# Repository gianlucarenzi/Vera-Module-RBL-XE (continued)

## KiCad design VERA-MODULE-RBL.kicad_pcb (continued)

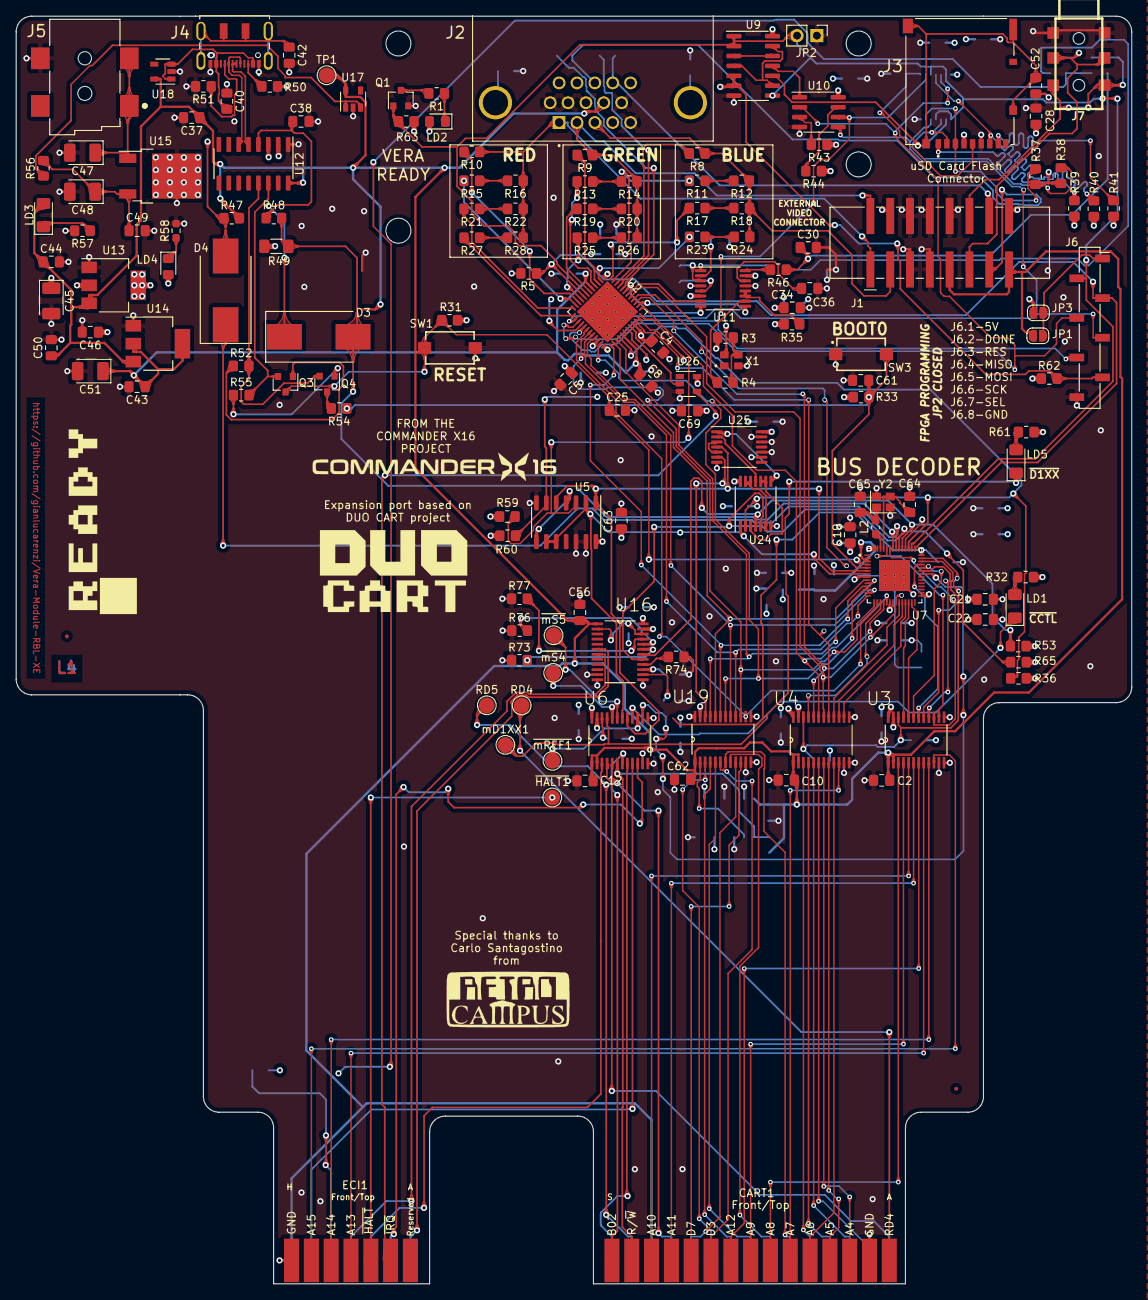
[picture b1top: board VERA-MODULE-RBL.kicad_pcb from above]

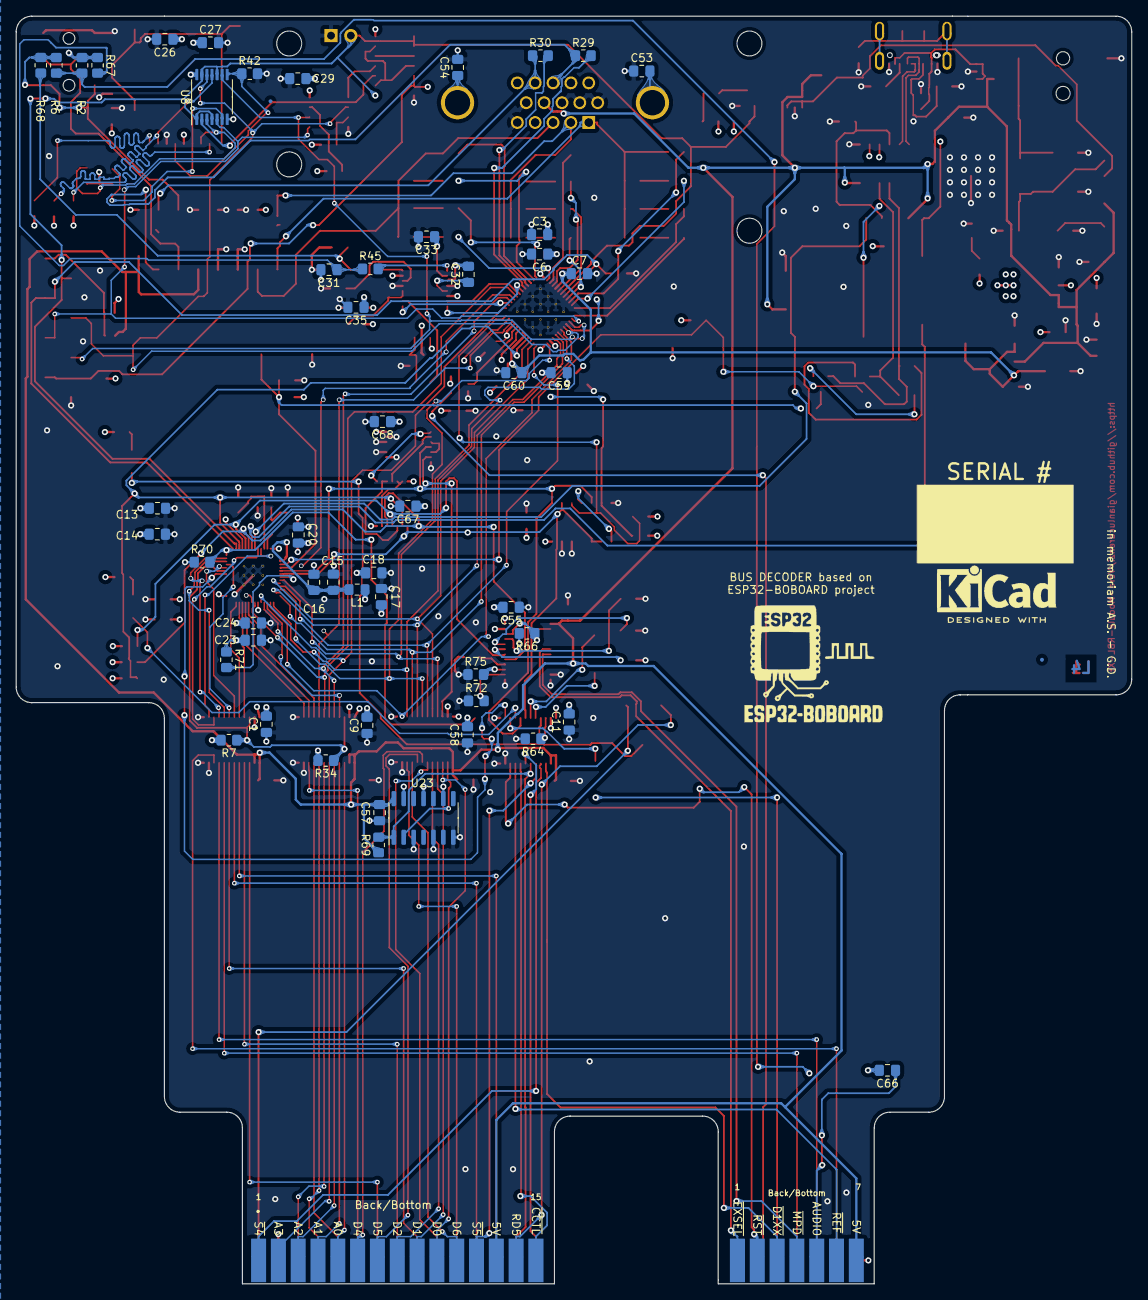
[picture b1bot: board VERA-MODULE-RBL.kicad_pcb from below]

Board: 4 copper layers, 143.0 x 162.5 mm, 213 parts (57 on the bottom side), 195 nets.

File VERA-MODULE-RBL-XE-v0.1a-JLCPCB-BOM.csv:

Comment,Designator,Footprint,LCSC
10uF,"C13,C15,C17,C19,C21,C24",Capacitor_SMD:C_1206_3216Metric_Pad1.33x1.80mm_HandSolder,C363964
100nF,"C14,C16,C18,C20,C22,C23,C25,C27,C28,C29,C38,C40,C42,C44,C46,C49,C50,C52,C53,C54",Capacitor_SMD:C_1206_3216Metric_Pad1.33x1.80mm_HandSolder,C2858001
4.7uF,"C26,C34,C35",Capacitor_SMD:C_1206_3216Metric_Pad1.33x1.80mm_HandSolder,C33546020
2.2uF,C36,Capacitor_SMD:C_1206_3216Metric_Pad1.33x1.80mm_HandSolder,C577211
22uF,C37,Capacitor_SMD:C_1206_3216Metric_Pad1.33x1.80mm_HandSolder,C6119967
20pF,"C39,C41",Capacitor_SMD:C_1206_3216Metric_Pad1.33x1.80mm_HandSolder,C5137576
1uF,"C1,C2,C3,C4,C5,C6,C7,C8,C9,C10,C11,C12,C30,C31,C32,C33,C43,C55,C56,C57,C58,C59,C60",Capacitor_SMD:C_1206_3216Metric_Pad1.33x1.80mm_HandSolder,C377070
10uF-35V,C47,Capacitor_Tantalum_SMD:CP_EIA-3528-12_Kemet-T_Pad1.50x2.35mm_HandSolder,C8017
10uF-20V,"C45,C48,C51",Capacitor_Tantalum_SMD:CP_EIA-3528-12_Kemet-T_Pad1.50x2.35mm_HandSolder,C8017
DIOSCH20V,"D3,D4",Diode_SMD:D_SMC_Handsoldering,C236151
CONN_SMD_02x08_Odd_Even_2.54mm,J1,RetroBitLab:PinSocket_2x08_P2.54mm_Vertical_SMD,C3975153
DS1038-15FBNSiA74-0CC,J2,RetroBitLab:CONNFLY_DS1038-15FBNSIA74-0CC,C75754
CONN_DM3AT-SF-PEJM5,J3,RetroBitLab:HRS_DM3AT-SF-PEJM5,C114218
DX07S016JA1R1500,J4,RetroBitLab:JAE_DX07S016JA1R1500,C3197885
PJ-002AH-SMT-TR,J5,RetroBitLab:CUI_PJ-002AH-SMT-TR,C22434687
CONN_SMD_01x08_Staggered_2.54mm,J6,Connector_PinSocket_2.54mm:PinSocket_1x08_P2.54mm_Vertical_SMD_Pin1Right,C42380985
SJ-3523-SMT-TR,J7,RetroBitLab:CONN_AUDIO_CUI_SJ-3523-SMT-TR,C4991872
FB0805100R100MHZ4A,L1,Inductor_SMD:L_0805_2012Metric_Pad1.15x1.40mm_HandSolder,C15957
RED,"LD1,LD3,LD5",LED_SMD:LED_1206_3216Metric_Pad1.42x1.75mm_HandSolder,C965822
GREEN,"LD2,LD4",LED_SMD:LED_0805_2012Metric_Pad1.15x1.40mm_HandSolder,C84260
MOSFET-BSS138-SOT-23,Q1,Package_TO_SOT_SMD:SOT-23,C82045
"BC817,SOT-23","Q3,Q4",Package_TO_SOT_SMD:SOT-23,C20069154
2K7,R1,Resistor_SMD:R_1206_3216Metric_Pad1.30x1.75mm_HandSolder,C6757641
2K,"R11,R13,R15",Resistor_SMD:R_1206_3216Metric_Pad1.30x1.75mm_HandSolder,C133543
150R,"R12,R14,R16",Resistor_SMD:R_1206_3216Metric_Pad1.30x1.75mm_HandSolder,C137387
160R,"R18,R20,R22",Resistor_SMD:R_1206_3216Metric_Pad1.30x1.75mm_HandSolder,C2933602
910R,"R17,R19,R21",Resistor_SMD:R_1206_3216Metric_Pad1.30x1.75mm_HandSolder,C5713461
27R,"R24,R26,R28",Resistor_SMD:R_1206_3216Metric_Pad1.30x1.75mm_HandSolder,C17946
820R,"R29,R30",Resistor_SMD:R_1206_3216Metric_Pad1.30x1.75mm_HandSolder,C2933759
50R,"R3,R4",Resistor_SMD:R_1206_3216Metric_Pad1.30x1.75mm_HandSolder,C2984401
330R,"R32,R61",Resistor_SMD:R_1206_3216Metric_Pad1.30x1.75mm_HandSolder,C114944
10K,"R33,R34,R62",Resistor_SMD:R_0805_2012Metric_Pad1.20x1.40mm_HandSolder,C84376
47K,"R37,R38,R39,R40,R41,R42,R43,R44",Resistor_SMD:R_1206_3216Metric_Pad1.30x1.75mm_HandSolder,C25833
560R,"R45,R46,R67,R68",Resistor_SMD:R_1206_3216Metric_Pad1.30x1.75mm_HandSolder,C2759125
10K,"R2,R5,R6,R7,R35,R36,R47,R48,R53,R63,R64,R65,R66",Resistor_SMD:R_1206_3216Metric_Pad1.30x1.75mm_HandSolder,C17902
5K1,"R50,R51",Resistor_SMD:R_1206_3216Metric_Pad1.30x1.75mm_HandSolder,C163372
220R,R54,Resistor_SMD:R_1206_3216Metric_Pad1.30x1.75mm_HandSolder,C137353
2K2,"R52,R55",Resistor_SMD:R_1206_3216Metric_Pad1.30x1.75mm_HandSolder,C114933
0R,R56,Resistor_SMD:R_1206_3216Metric_Pad1.30x1.75mm_HandSolder,C17888
510R,"R23,R25,R27,R57",Resistor_SMD:R_1206_3216Metric_Pad1.30x1.75mm_HandSolder,C2933720
330R,R58,Resistor_SMD:R_0603_1608Metric_Pad0.98x0.95mm_HandSolder,C105881
4K7,"R31,R59,R60",Resistor_SMD:R_1206_3216Metric_Pad1.30x1.75mm_HandSolder,C17936
4K3,"R8,R9,R10",Resistor_SMD:R_1206_3216Metric_Pad1.30x1.75mm_HandSolder,C2933704
SPST2P,SW1,RetroBitLab:SPST-7.3x3.9x2.5-WUERTH-434121025816,C318911
"SPST_SWITCH_SMD_4P,4.1x5.4mm",SW2,RetroBitLab:SW_DIP_SPSTx02_DSHP02TS-S,C319052
W25Q16JVSNIQ,U10,Package_SO:SOIC-8_3.9x4.9mm_P1.27mm,C2456211
WM8524CGEDT,U11,Package_SO:TSSOP-16_4.4x5mm_P0.65mm,C146242
USBCH340T,U12,Package_SO:SSOP-20_5.3x7.2mm_P0.65mm,C8689
AMS1117-3.3,U13,Package_TO_SOT_SMD:SOT-223-3_TabPin2,C6186
AMS1117-1.2,U14,Package_TO_SOT_SMD:SOT-223-3_TabPin2,C347218
L7805,U15,Package_TO_SOT_SMD:TO-252-2,C110908
MAX40200AUK,"U17,U18",Package_TO_SOT_SMD:SOT-23-5,C47118006
ICE40UP5K-SG48ITR,U2,RetroBitLab:QFN-48-1EP_7x7mm_P0.5mm_EP5.6x5.6mm,C2678152
TXS0108EPW,"U1,U3,U4,U6,U16",Package_SO:TSSOP-20_4.4x6.5mm_P0.65mm,C17206
CD4011B,"U5,U9",Package_SO:SOIC-14_3.9x8.7mm_P1.27mm,C194334
ESP32-PICO-D4,U7,RetroBitLab:ESP32-PICO-D4,C193707
"74CBTLV3126PW,118",U8,Package_SO:TSSOP-14_4.4x5mm_P0.65mm,C543078
ECS-2033-250-BN,X1,RetroBitLab:OSC_ECS-2033-250-BN,C2441279
12MHzC,Y1,Crystal:Crystal_SMD_EuroQuartz_MT-4Pin_3.2x2.5mm,C9002

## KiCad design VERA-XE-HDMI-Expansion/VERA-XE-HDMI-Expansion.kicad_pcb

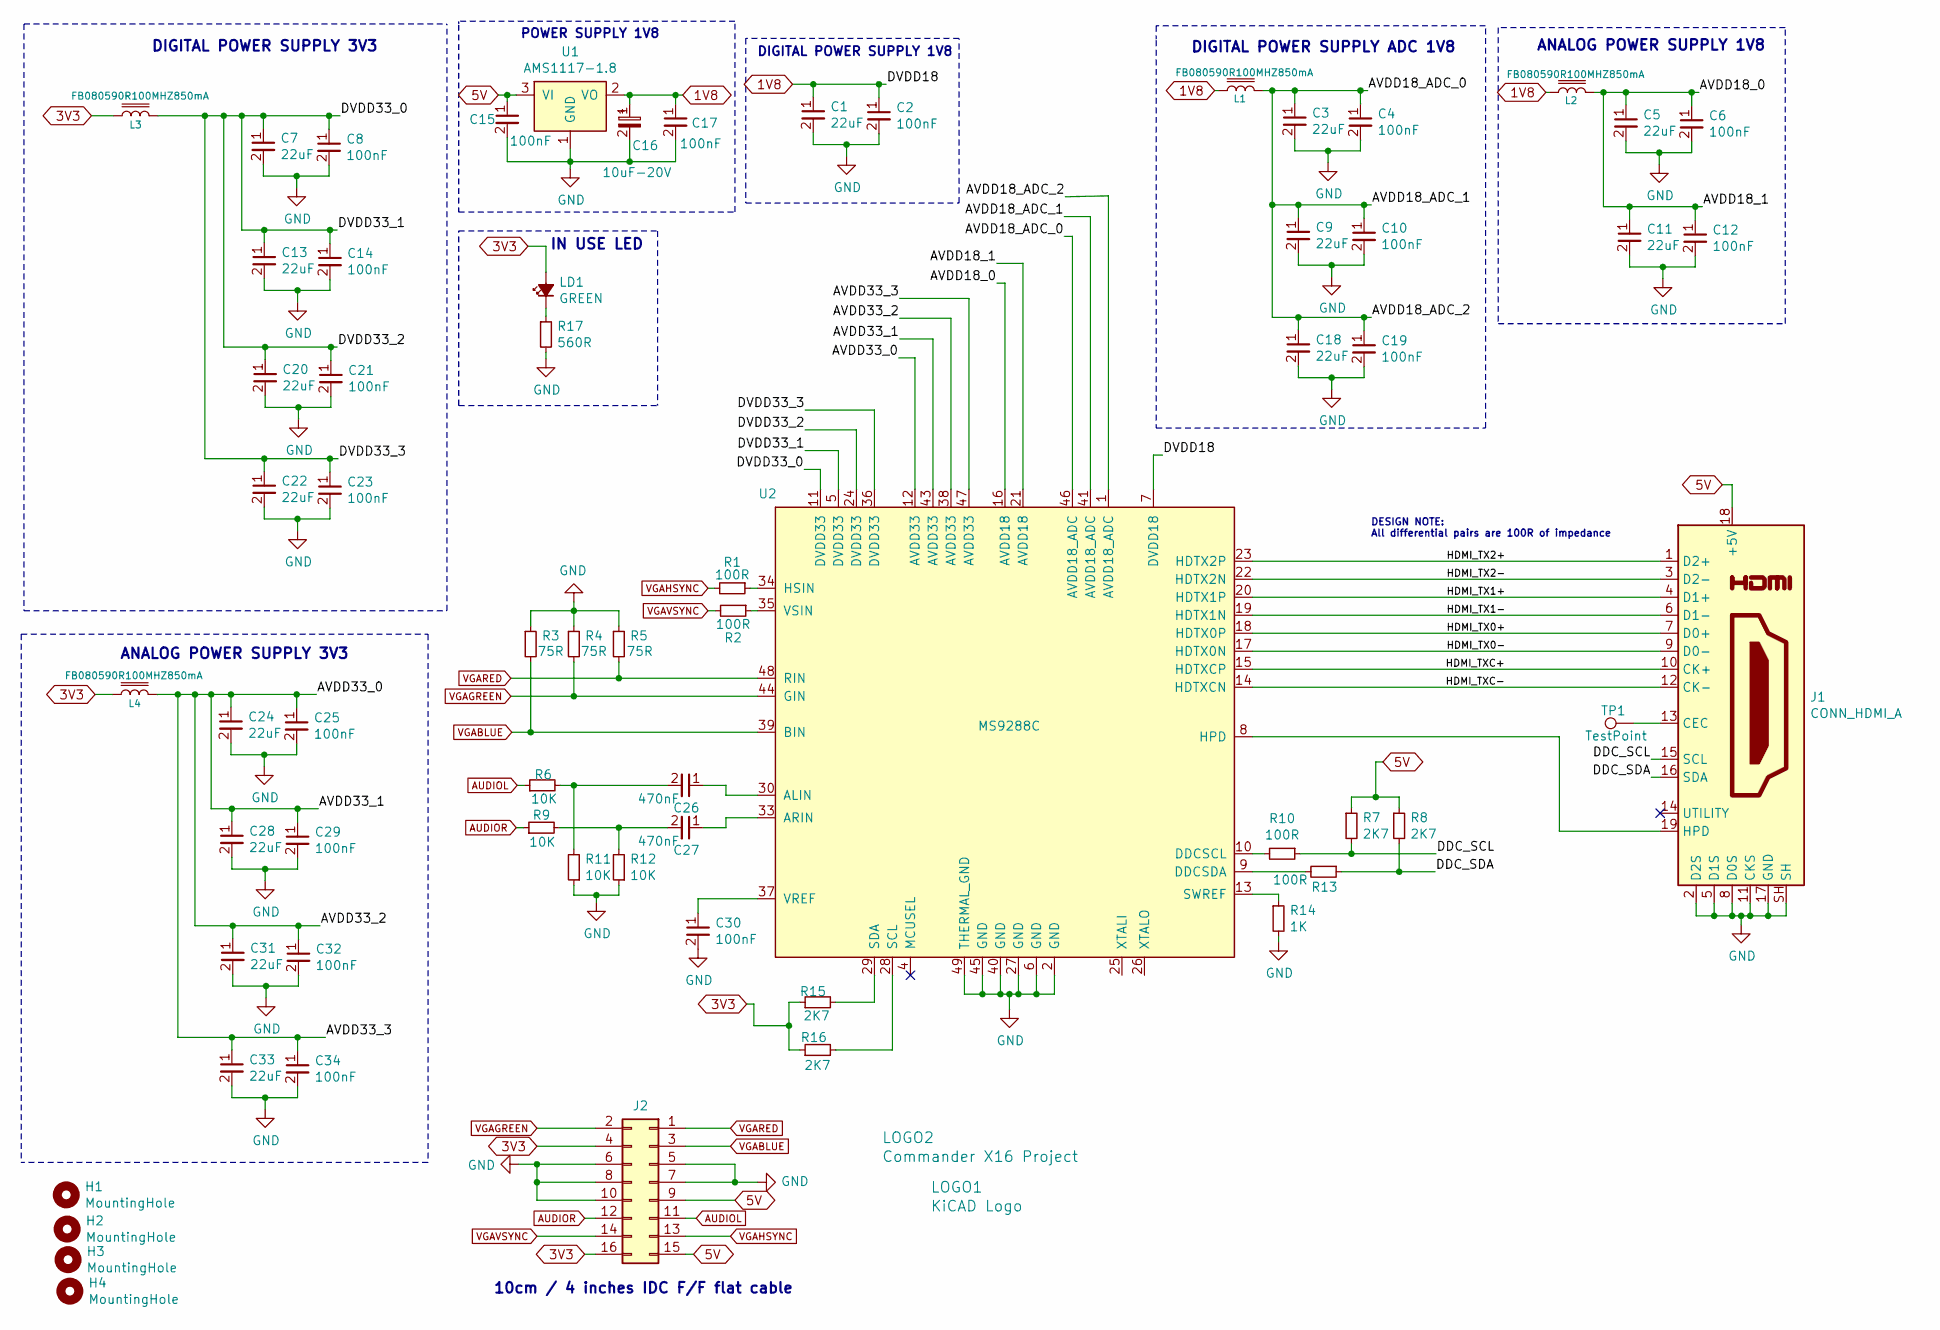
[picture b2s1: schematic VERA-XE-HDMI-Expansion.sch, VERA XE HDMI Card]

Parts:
C1, C3, C5, C7, C9, C11, C13, C18, C20, C22, C24, C28, C31, C33: 22uF; C_0805_2012Metric_Pad1.18x1.45mm_HandSolder; LCSC C86817
C2, C4, C6, C8, C10, C12, C14, C15, C17, C19, C21, C23, C25, C29, C30, C32, C34: 100nF; C_0805_2012Metric_Pad1.18x1.45mm_HandSolder; LCSC C840116
C16: 10uF-20V; CP_EIA-3528-12_Kemet-T_Pad1.50x2.35mm_HandSolder; LCSC C8017
C26, C27: 470nF; C_0805_2012Metric_Pad1.18x1.45mm_HandSolder; LCSC C106843
H1, H2, H3, H4: MountingHole; MountingHole_3.2mm_M3
J1: CONN_HDMI_A; CONN_HDMI-A; LCSC C720616
J2: CONN_SMD_HEADER_BOX_02x08_Odd_Even_2.54mm; PinHeader_BOX_2x08_P2.54mm_Vertical_SMD; LCSC C2685064
L1, L2, L3, L4: FB080590R100MHZ850mA; L_0805_2012Metric_Pad1.15x1.40mm_HandSolder; LCSC C50325938
LD1: GREEN; LED_0805_2012Metric_Pad1.15x1.40mm_HandSolder; LCSC C84260
LOGO1: KiCAD Logo; KiCad-Logo2_6mm_SilkScreen
LOGO2: Commander X16 Project; x16logo
R1, R2, R10, R13: 100R; R_0805_2012Metric_Pad1.20x1.40mm_HandSolder; LCSC C17408
R3, R4, R5: 75R; R_0805_2012Metric_Pad1.20x1.40mm_HandSolder; LCSC C20142801
R6, R9, R11, R12: 10K; R_0805_2012Metric_Pad1.20x1.40mm_HandSolder; LCSC C84376
R7, R8, R15, R16: 2K7; R_0603_1608Metric_Pad0.98x0.95mm_HandSolder; LCSC C491210
R14: 1K; R_0805_2012Metric_Pad1.20x1.40mm_HandSolder; LCSC C17513
R17: 560R; R_0603_1608Metric_Pad0.98x0.95mm_HandSolder; LCSC C114629
TP1: TestPoint; TestPoint_Pad_1.0x1.0mm
U1: AMS1117-1.8; SOT-223-3_TabPin2; LCSC C6185
U2: MS9288C; LCSC C2914316

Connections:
1V8: C1.1, C2.1, C16.1, C17.1, L1.1, L2.1, U1.2 (VO), U2.7 (DVDD18)
3V3: J2.4, J2.16, L3.1, L4.1, LD1.2 (A), R15.1, R16.1
5V: C15.1, J1.18 (+5V), J2.9, J2.15, R7.1, R8.1, U1.3 (VI)
/AVDD18_0: C5.1, C6.1, C11.1, C12.1, L2.2, U2.16 (AVDD18), U2.21 (AVDD18)
/AVDD18_ADC_0: C3.1, C4.1, C9.1, C10.1, C18.1, C19.1, L1.2, U2.1 (AVDD18_ADC), U2.41 (AVDD18_ADC), U2.46 (AVDD18_ADC)
/AVDD33_0: C24.1, C25.1, C28.1, C29.1, C31.1, C32.1, C33.1, C34.1, L4.2, U2.12 (AVDD33), U2.38 (AVDD33), U2.43 (AVDD33), U2.47 (AVDD33)
/DDC_SCL: J1.15 (SCL), R7.2, R10.1
/DDC_SDA: J1.16 (SDA), R8.2, R13.1
/DVDD33_0: C7.1, C8.1, C13.1, C14.1, C20.1, C21.1, C22.1, C23.1, L3.2, U2.5 (DVDD33), U2.11 (DVDD33), U2.24 (DVDD33), U2.36 (DVDD33)
/HDMI_TX0+: J1.7 (D0+), U2.18 (HDTX0P)
/HDMI_TX0-: J1.9 (D0-), U2.17 (HDTX0N)
/HDMI_TX1+: J1.4 (D1+), U2.20 (HDTX1P)
/HDMI_TX1-: J1.6 (D1-), U2.19 (HDTX1N)
/HDMI_TX2+: J1.1 (D2+), U2.23 (HDTX2P)
/HDMI_TX2-: J1.3 (D2-), U2.22 (HDTX2N)
/HDMI_TXC+: J1.10 (CK+), U2.15 (HDTXCP)
/HDMI_TXC-: J1.12 (CK-), U2.14 (HDTXCN)
AUDIOL: J2.11, R6.1
AUDIOR: J2.12, R9.1
GND: C1.2, C2.2, C3.2, C4.2, C5.2, C6.2, C7.2, C8.2, C9.2, C10.2, C11.2, C12.2, C13.2, C14.2, C15.2, C16.2, C17.2, C18.2, C19.2, C20.2, C21.2, C22.2, C23.2, C24.2, C25.2, C28.2, C29.2, C30.2, C31.2, C32.2, C33.2, C34.2, J1.2 (D2S), J1.5 (D1S), J1.8 (D0S), J1.11 (CKS), J1.17 (GND), J1.SH, J2.5, J2.6, J2.7, J2.8, J2.10, R3.1, R4.1, R5.1, R11.1, R12.1, R14.2, R17.2, U1.1 (GND), U2.2 (GND), U2.6 (GND), U2.27 (GND), U2.40 (GND), U2.45 (GND), U2.49 (THERMAL_GND)
unnamed: C26.1, U2.30 (ALIN)
unnamed: C26.2, R6.2, R11.2
unnamed: C27.1, U2.33 (ARIN)
unnamed: C27.2, R9.2, R12.2
unnamed: C30.1, U2.37 (VREF)
unnamed: J1.13 (CEC), TP1.1
unnamed: J1.19 (HPD), U2.8 (HPD)
unnamed: LD1.1 (K), R17.1
unnamed: R1.1, U2.34 (HSIN)
unnamed: R2.1, U2.35 (VSIN)
unnamed: R10.2, U2.10 (DDCSCL)
unnamed: R13.2, U2.9 (DDCSDA)
unnamed: R14.1, U2.13 (SWREF)
unnamed: R15.2, U2.29 (SDA)
unnamed: R16.2, U2.28 (SCL)
VGABLUE: J2.3, R3.2, U2.39 (BIN)
VGAGREEN: J2.2, R4.2, U2.44 (GIN)
VGAHSYNC: J2.13, R1.2
VGARED: J2.1, R5.2, U2.48 (RIN)
VGAVSYNC: J2.14, R2.2

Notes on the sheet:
DIGITAL POWER SUPPLY 3V3
ANALOG POWER SUPPLY 3V3
DIGITAL POWER SUPPLY 1V8
DIGITAL POWER SUPPLY ADC 1V8
ANALOG POWER SUPPLY 1V8
DESIGN NOTE: All differential pairs are 100R of impedance
POWER SUPPLY 1V8
10cm / 4 inches IDC F/F flat cable
IN USE LED

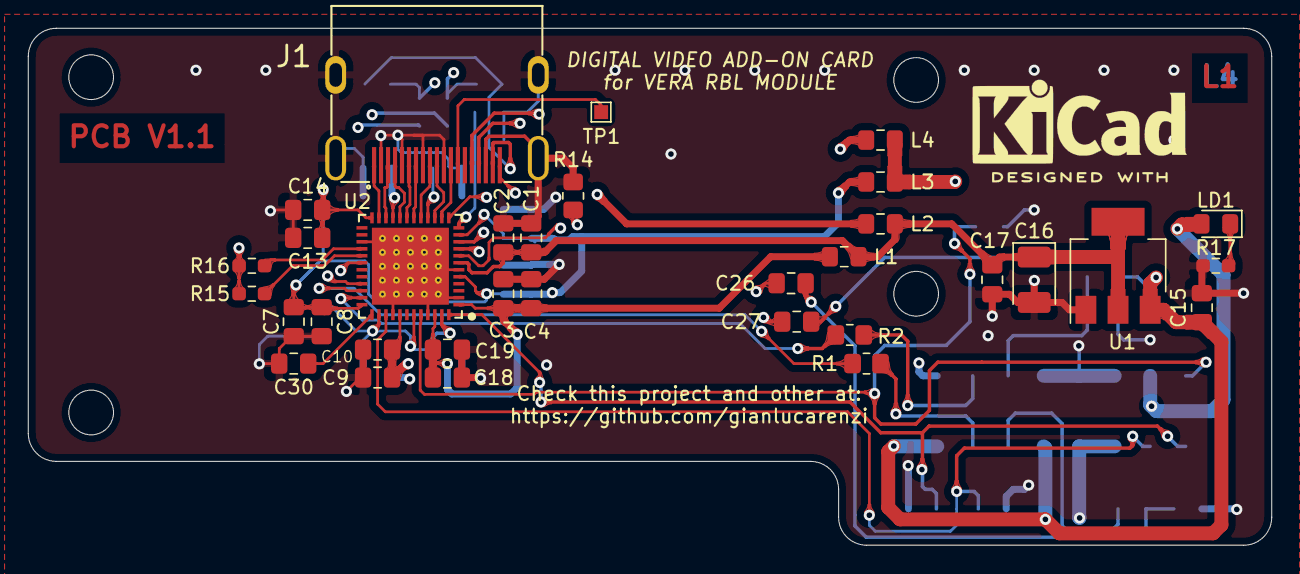
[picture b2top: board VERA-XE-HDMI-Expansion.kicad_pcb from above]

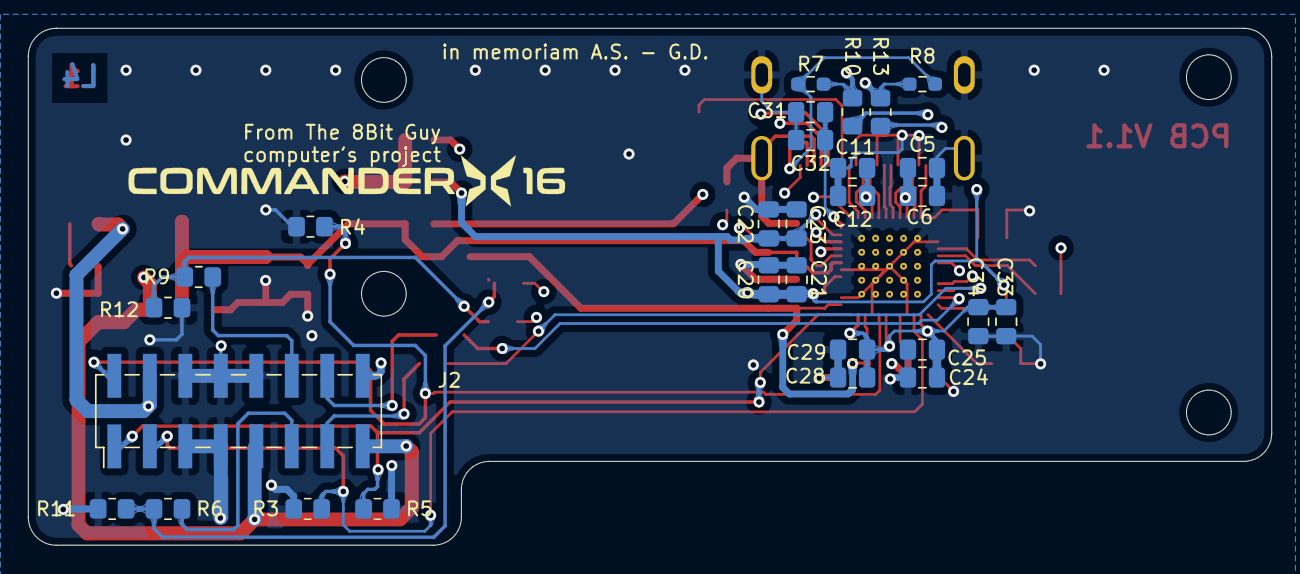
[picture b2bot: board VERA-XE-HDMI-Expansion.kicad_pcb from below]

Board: 4 copper layers, 89.0 x 37.0 mm, 67 parts (29 on the bottom side), 40 nets.

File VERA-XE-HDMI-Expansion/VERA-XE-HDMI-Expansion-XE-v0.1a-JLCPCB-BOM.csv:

Comment,Designator,Footprint,LCSC
10uF-20V,C16,Capacitor_Tantalum_SMD:CP_EIA-3528-12_Kemet-T_Pad1.50x2.35mm_HandSolder,C8017
470nF,"C26,C27",Capacitor_SMD:C_0805_2012Metric_Pad1.18x1.45mm_HandSolder,C106843
22uF,"C1,C3,C5,C7,C9,C11,C13,C18,C20,C22,C24,C28,C31,C33",Capacitor_SMD:C_0805_2012Metric_Pad1.18x1.45mm_HandSolder,C86817
100nF,"C2,C4,C6,C8,C10,C12,C14,C15,C17,C19,C21,C23,C25,C29,C30,C32,C34",Capacitor_SMD:C_0805_2012Metric_Pad1.18x1.45mm_HandSolder,C840116
CONN_HDMI_A,J1,RetroBitLab:CONN_HDMI-A,C720616
CONN_SMD_HEADER_02x08_Odd_Even_2.54mm,J2,Connector_PinHeader_2.54mm:PinHeader_2x08_P2.54mm_Vertical_SMD,C32713288
FB080590R100MHZ850mA,"L1,L2,L3,L4",Inductor_SMD:L_0805_2012Metric_Pad1.15x1.40mm_HandSolder,C50325938
GREEN,LD1,LED_SMD:LED_0805_2012Metric_Pad1.15x1.40mm_HandSolder,C84260
1K,R14,Resistor_SMD:R_0805_2012Metric_Pad1.20x1.40mm_HandSolder,C17513
2K7,"R7,R8,R15,R16",Resistor_SMD:R_0603_1608Metric_Pad0.98x0.95mm_HandSolder,C491210
560R,R17,Resistor_SMD:R_0603_1608Metric_Pad0.98x0.95mm_HandSolder,C114629
100R,"R1,R2,R10,R13",Resistor_SMD:R_0805_2012Metric_Pad1.20x1.40mm_HandSolder,C17408
75R,"R3,R4,R5",Resistor_SMD:R_0805_2012Metric_Pad1.20x1.40mm_HandSolder,C20142801
10K,"R6,R9,R11,R12",Resistor_SMD:R_0805_2012Metric_Pad1.20x1.40mm_HandSolder,C84376
AMS1117-1.8,U1,Package_TO_SOT_SMD:SOT-223-3_TabPin2,C6185
MS9288C,U2,RetroBitLab:MS9288C,C2914316

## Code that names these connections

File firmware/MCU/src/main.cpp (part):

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 * =========================================================================== */

/* --- Bank 0 Signals (GPIO 0-31) --- */
#define PIN_PHI2        1    /* CPU Clock Phase 2 (Pin 6) */
#define PIN_RW          2    /* Read/Write, High = Read (Pin 7) */

/* D0-D7: GPIO 4 to 11 (Pins 9-16, contiguous in Bank 0): D0 = GPIO 4 */
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#define PIN_CDONE       39   /* Vera Programmed Status Input (Pin 44) */
#define PIN_DEV_SEL_N   40   /* Vera Chip Select Output (Pin 45, active LOW) */
#define PIN_EXTSEL_N    41   /* Atari MMU Disable Output (Pin 47, active LOW) */
#define PIN_MPD         42   /* Math Pack Disable — disables internal Atari Math Pack ROM $D800-$DFFF (Pin 48, active LOW) */
#define PIN_A14         45   /* Address Bit 14 (Pin 51) */
#define PIN_A15         46   /* Address Bit 15 (Pin 52) */
#define PIN_ABUS_OE_N   47   /* ~OE of U3 (A8-A15) and U4 (A0-A7), 10 kΩ pull-ups R7/R34 (Pin 37, active LOW) */
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 * (ee.get_gpio_in / ee.wr_mask_gpio_out bypass the APB bus: ~1 cycle).
 *
 * Input channels  (bit index in cpu_ll_read_dedic_gpio_in() result):
 *   Ch 0 = PHI2 (GPIO 1), Ch 1 = R/W (GPIO 2), Ch 2-7 = A10-A15
 *   The GPIO matrix feeds the dedicated inputs without taking the pins away:
 *   the same signals stay visible in GPIO.in / GPIO.in1.
 *
 * Output channels (bit index in cpu_ll_write_dedic_gpio_mask() mask/val):
 *   Ch 0 = DEV_SEL_N  (GPIO 40)  active LOW
 *   Ch 1 = EXTSEL_N   (GPIO 41)  active LOW
 *   Ch 2 = MPD        (GPIO 42)  active LOW
 *
 * Input and output channel spaces are independent on ESP32-S3.
 * Channel bits (DEDIC_IN_* / DEDIC_OUT_*) are defined in bus_decode.h.
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 * =========================================================================== */
#define LOG_RING_SIZE 64u   /* power of two */

#define EVT_LATCH 0   /* VCS/CCTL latch state change */
#define EVT_REG   1   /* VERA register ($D1xx) access */

/* flags: bit0=write(1)/read(0)  bit1=latch state (EVT_LATCH)  bit2=MPD asserted  bit3=EXTSEL asserted */
typedef struct
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}

/*
 * PHI2 edge waits: one ee.get_gpio_in and one bit branch per sample
 * (3 cycles), the shortest polling loop.  They return the last sample.
 */
static inline __attribute__((always_inline)) void wait_phi2_high(void)
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     * Input  bundle: [PHI2, R/W, A10..A15]       → input  ch 0-7
     * Output bundle: [DEV_SEL_N, EXTSEL_N, MPD]  → output ch 0-2
     */
    static const int dedic_in_pins[]  = { PIN_PHI2, PIN_RW, PIN_A10, PIN_A11,
                                          PIN_A12, PIN_A13, PIN_A14, PIN_A15 };
    static const int dedic_out_pins[] = { PIN_DEV_SEL_N, PIN_EXTSEL_N, PIN_MPD };
    dedic_gpio_bundle_handle_t dedic_in_bundle, dedic_out_bundle;
    const dedic_gpio_bundle_config_t in_cfg =
    {
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            {
                /* VERA drives the bus: sample it just before PHI2 falls. */
                uint32_t last = lo, now;
                while ((now = GPIO.in) & (1UL << PIN_PHI2))
                    last = now;
                uint8_t fl = 0x00;  /* read */
                if (!(c & DEDIC_OUT_MPD))    fl |= 0x04;
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    gpio_reset_pin((gpio_num_t)PIN_CDONE);     /* GPIO 39 */
    gpio_reset_pin((gpio_num_t)PIN_DEV_SEL_N); /* GPIO 40 */
    gpio_reset_pin((gpio_num_t)PIN_EXTSEL_N);  /* GPIO 41 */
    gpio_reset_pin((gpio_num_t)PIN_MPD);       /* GPIO 42 */

    /* Hold the VERA in reset immediately; it is released below.  The Atari
     * cannot be held (RST is the 130XE NE555 output, see PIN_ARST_IN). */
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    cfg.mode         = GPIO_MODE_INPUT;

    /* Bank 0 inputs: PHI2, RW, D0-D7, A0-A9 */
    cfg.pin_bit_mask = (1ULL << PIN_PHI2) | (1ULL << PIN_RW) | DBUS_MASK | ABUS_LO_MASK;
    gpio_config(&cfg);

    /* Bank 1 inputs: A10-A15, CDONE, Atari RST */
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    pinMode(PIN_DEV_SEL_N, OUTPUT);
    digitalWrite(PIN_DEV_SEL_N, HIGH);

    pinMode(PIN_MPD, OUTPUT);
    digitalWrite(PIN_MPD, HIGH);

    /*
     * VERA bring-up:
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
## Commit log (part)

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2025-09-10 Update to more available components by LCSC
2025-09-12 Removed level shifters by MOSFET
2025-09-17 Modified the 1.5V LDO to 1.2V LDO as in X65 and Vera Module projects. Added a 3.5mm audio jack stereo. To check if there are issues with the ATARI connected AUDIO Mixer
2025-09-17 Moved the FPGA programming box from vera-fpga-flash.sch
2025-09-18 First commit from RetroBit Lab Computer. This file will be ignored by Git, as it has hardcoded the path to the project.
2025-09-19 Update date on schematics
2025-09-19 Added two 560R resistors on the AUDIO_[L/R] lines as in X65 schematics Audio Resistor in line changed from 2K7 to 10K
2025-09-23 Update date on schematics Added a label for Serial Number (by hand)
2025-09-23 CD4011B instead of IC74HC00 NAND Gate (LCSC availability) The pinout is different! Added Label 2mmx1mm LBL1
2025-09-24 Frames added
2025-09-24 Update the programming section
2025-09-29 Changed the code for 330R 1206 from LCSC
2025-09-30 Fit all project schematics in an A4 size sheet
2025-09-30 Changed LCSC code for 27R
2025-10-02 Error
2025-10-06 optimized for execution time
2025-10-08 More code optimizations
2025-10-08 ANSI Color update
2025-10-17 Ignored fp-info-cache
2025-10-17 Needed for holes for spacers
2025-10-17 Updated messages
2025-10-17 Some capacitors changed from 1206 to 0805 due to shortage of the bigger ones
2025-10-20 Size changes. WIP
2025-10-23 Capacitor 10uF 0805 change LCSC code. These are more common
2025-10-23 Corrected a TearDrop manually
2025-10-27 Removed. Those should not be needed
2025-10-28 Added cleanup report
2025-10-28 Auto-generated
2025-10-29 Generated when exporting BOM from Schematics. This should be generated by a CLI
2025-10-29 Removed. Not needed now
2025-10-29 Ignore the cache.lib file
2025-10-29 Autogenerated v1.1
2025-10-29 Updated to new holes for the Digital Video Interface (HDMI?) and with rounded corners
2025-10-29 Python3 path for system
2025-10-29 Added more artifact to be ignored
2025-10-29 Ignored built executables (eeplot and eeshow)
2026-05-05 Updated for Datasheet
2026-05-08 Updated DEVID MASK to 0x80 (bit 7)
2026-05-08 Ignore intermediate artifact from build
2026-05-08 Maximum ROM Size is 2K ($0800)
2026-05-08 Typo and missing includes
2026-05-28 Date updated
2026-05-28 FPGA always deactive. It will be relased to run by MCU ESP32 when ready
2026-05-28 Need 9 bytes of address space to have more than 256 bytes of addressing (needed for External Device RAM Space)
2026-06-08 All Power Voltage references are by Global Label (5V and 3V3)
2026-06-08 after saving
2026-06-09 Add dual-MCU support (ESP32-S3FN8 + ESP32-classic) with QFN56 pin mapping
    - Rewrite main.cpp with #if MCU_ESP32_S3 / MCU_ESP32_CLASSIC blocks: separate
    pin defines, DBUS_MASK, DBUS_PINS[], decode_addr/data/offset_cctl, and
    gpio_config bitmasks for each target; build_drive_lut and Serial.begin use
    the MCU-specific constants at compile time
    - Add 4 PlatformIO environments in platformio.ini: nodemcu-pbi, nodemcu-cctl,
    esp32s3fn8-pbi, esp32s3fn8-cctl; all pinned to espressif32@6.6.0 to avoid
2026-06-09 PBI firmware: add MPD, RAM_SEL_N, and bus contention fix
    - ESP32-S3FN8: add PIN_RAM_SEL_N (GPIO40/MTDO) and PIN_MPD (GPIO42/MTMS)
    - Assert MPD before bus_drive() for all PBI reads (ROM, RAM, int_regs, VERA)
    to prevent bus contention when the Atari MMU has not tristated its buffer
    - Add 512-byte ram_pbi[] IRAM buffer served at $D600-$D7FF when VCS latch active
    - MPD_ASSERT/DEASSERT use GPIO.out1_w1tc/w1ts (bank-1 GPIO32+ registers)
    - DECODE_IS_RAM reads GPIO40 from g_hi (bank-1 snapshot)
2026-06-09 Fix: comportamento corretto EXTSEL_N e MPD nel PBI loop
    EXTSEL_N (GPIO0):
    - Non e' un segnale persistente legato allo stato del latch
    - Si asserta per-ciclo quando selected && ((is_d1xx && !is_d1ff) || is_ram)
    - Disabilita MMU/Freddie per accesso D1xx ($D100-$D1FE) e RAM $D600-$D7FF
    - Si deasserta sempre a fine ciclo insieme a DEV_SEL_N
    MPD (GPIO42, Math Pack Disable):
2026-06-09 doc: aggiorna analisi LaTeX con mapping pin revisionato ESP32-S3FN8
    - Code listing 1: aggiunge PIN_RAM_SEL_N=40, PIN_MPD=42, macro
    MPD_ASSERT/DEASSERT (bank-1), DECODE_IS_RAM, decode_addr completo
    A0-A10, stub MCU_ESP32_CLASSIC con warning
    - Code listing 2 (MonitorTask): EXTSEL_N per-ciclo (D1xx e RAM),
    MPD solo per ROM $D800-$DFFF, gestione lettura ROM/RAM/int_regs,
    deassert tutti i segnali a fine ciclo
2026-06-09 chore: remove support for ESP32 Classic (NodeMCU/PICO-D4)
    - Removed NodeMCU-specific build environments from platformio.ini.
    - Cleaned up main.cpp to remove MCU_ESP32_CLASSIC logic and pin mappings.
    - Updated documentation (Vera_Module_Analisys.ITA.tex, PIN-MAPPING.md, README.md) to reflect exclusive support for ESP32-S3FN8.
    - Verified successful builds for esp32s3fn8-pbi and esp32s3fn8-cctl.
2026-06-10 updated for ESP32-S3FN8
2026-06-10 build: compila vera_pbi_handler.s e genera vera_pbi_handler.h per ESP32
    Makefile aggiornato: sorgente pbi-driver.s → vera_pbi_handler.s,
    inc/vera_common.inc aggiunto come dipendenza esplicita, nomi output
    e guard/array nel .h generato rinominati di conseguenza.
2026-06-10 doc: aggiorna firmware/MCU/README con riferimento al driver 6502 vera_pbi_handler
2026-06-10 feat: decodifica bus indirizzi completa a 16 bit (A0-A15)
    - main.cpp: aggiunge PIN_A12-A15 (GPIO 33, 34, 47, 48); decode_addr()
    esteso a 16 bit sfruttando la stessa lettura GPIO.in1.val già presente
    (zero cicli APB aggiuntivi); confronti is_d1xx/is_d6xx/is_d8xx e CCTL
    aggiornati con indirizzi completi $Dxxx — nessuna ambiguità di pagina
    - PIN-MAPPING.md: aggiunge sezione A12-A15 con U4 TXS0108E, snippet
    firmware decode a 16 bit, nota PCB routing, QFN56 e GPIO disponibili
2026-06-10 feat: alloca extended_rambo_256k (256 KB) in IRAM BSS senza costo Flash
    Usa __attribute__((section(".iram0.bss"))) invece di IRAM_ATTR:
    il buffer risiede in IRAM (0x4038382C) e viene zero-inizializzato
    dal boot senza occupare spazio nella Flash.
2026-06-10 refactor: rimuovi BUS_MODE e unifica PBI + CCTL in un unico firmware runtime
    Eliminato il preprocessore condizionale BUS_MODE: lo stesso binario gestisce
    $D1xx (PBI/VERA) e $D5xx (CCTL) decodificando il bus indirizzi A0-A15 a runtime.
    Consolidato platformio.ini da due ambienti (pbi/cctl) a uno solo (esp32s3fn8).
2026-06-10 docs: aggiorna PIN-MAPPING con modalità PBI/CCTL, rimuovi int_regs
    Decode snippet aggiornato: tabella VERA_BOARD_IS_PBI, range CCTL $D500-$D5FF
    con latch $D5FF, niente più riferimento a int_regs. Segnali EXTSEL_N e MPD
    annotati come "solo PBI mode"; DEV_SEL_N descrive entrambe le modalità.
2026-06-10 feat: implementa emulatore RAMbo 256 KB bank-switched a $4000-$7FFF
    Snoop PORTB ($D301) in PBI mode: bit4=0 attiva RAMbo, bit6/5/3/2 selezionano
    il banco 0-15. EXTSEL_N assertito per sopprimere la RAM interna Atari.
    Lettura: bus_drive da extended_rambo_256k[bank*16K + offset].
    Scrittura: store in extended_rambo_256k[bank*16K + offset].
    portb_rambo inizializzato a 0xFF (RAMbo disabilitato al boot).
2026-06-10 docs: aggiorna documentazione per PIN_RAMBO_EN (GPIO 3)
    Rimuove ogni riferimento a USE_RAMBO_256K dalla documentazione.
    PIN_RAMBO_EN (GPIO 3, QFN56 pin 8) aggiunto a tutte le tabelle pin
    con descrizione pull-up/pull-down 10K. Aggiornati README principale
    (EN+IT), firmware/MCU/README.md e PIN-MAPPING.md (warnings, control
    signals, GPIO disponibili, pinout QFN56).
2026-06-10 docs: documenta sequenza di startup sincronizzata VERA/ATARI
    Aggiunta sezione 'Sequenza di startup' in firmware/MCU/README.md con
    i tre passi (CRESET, poll CDONE, ARESET) e nota sul comportamento di
    preemption del MonitorTask. Aggiornato README.md (EN+IT) con bullet
    'Startup sync' nella descrizione firmware ESP32.
2026-06-10 docs: add crystal oscillator section (XTAL_P pin 56, XTAL_N pin 55)
    New PIN-MAPPING.md § 5 documents the mandatory 40 MHz crystal circuit:
    pin assignment, load capacitor formula, optional series resistor, and
    PCB layout rules. XTAL pins added to the excluded-pin table (§ 7).
    Sections renumbered 5→6 (Level Shifting), 6→7 (GPIO), 7→8 (QFN56 pinout).
    firmware/MCU/README.md intro now warns about the crystal requirement.
2026-06-10 fix: add PBCTL ($D303) emulation; gate PORTB updates on CRB-2 bit
    The PIA 6520 exposes two registers at $D301 depending on PBCTL bit 2:
    CRB-2 = 0 → Data Direction Register (DDR) — writes must be ignored
    CRB-2 = 1 → Output Register (PORTB) — bank-selection writes
    Previously every write to $D301 updated PORTB, incorrectly treating DDR
    initialisation writes as bank selections. The fix adds a static PBCTL
    variable, snoops $D303 in the hot loop, and gates $D301 updates on bit 2.
2026-06-10 docs: spiega distinzione snooping passivo vs. pilotaggio attivo per RAMbo
    Aggiunta spiegazione in firmware/MCU/README.md, root README.md (EN+IT)
    e Vera_Module_Analisys.ITA.tex del motivo per cui l'ESP32 non entra in
    conflitto con il 6520 fisico: per $D301/$D303 l'ESP32 è un bus snooper
    passivo (non pilota mai D0-D7), mentre per $4000-$7FFF pilota attivamente
    via EXTSEL_N + bus dati. La tabella comparativa chiarisce anche perché il
    tracciamento di PBCTL è necessario: una write DDR e una write all'Output
2026-06-10 fix: correggi overflow pagine nel documento LaTeX
    - Tabella pin principale: \resizebox{\linewidth}{!} per adattare alla larghezza
    - Equazione RAMbo: multline* per spezzare la riga troppo lunga
    - Tabella XTAL pin: p{8cm} sulla colonna Note per permettere il wrapping
    - Tabella componenti XTAL: \resizebox{\linewidth}{!}
    - Flowchart: scale 0.65->0.50, node distance 1.6/1.2->1.2/1.0, gap phi2_low 3.5->2.5cm
    - Tabella snooping: \resizebox{\linewidth}{!}
2026-06-11 docs: rewrite FPGA README in English with full build and flash instructions
2026-06-11 fix: correggi VHDL e PCF per rispettare i 39 pin dell'UP5K-SG48
    - Rinomina RNW_ in RNW (GHDL 2008 vieta identificatori che terminano con _)
    - Riduce DIP_SEL da 3 a 2 bit (40 pin -> 39, entro il limite SG48)
    - PCF: sostituisce tutti i pin non validi per SG48 (1,7,22,24,29,30)
    con pin validi (6,26,37,38,39); rimosso DIP_SEL[2]
    - Bitstream generato con successo: 102 KB, fmax 62.72 MHz @ 25 MHz clock
2026-06-11 docs: aggiorna guida LaTeX con risultati di sintesi misurati
    - Tabella risorse con breakdown LC dettagliato da nextpnr
    (87 LC totali: 52 LUT4, 5 LUT4+DFF, 5 DFF, 21 CARRY, 3 legalise)
    - Tabella timing misurata: fmax 62.72 MHz, comb 28.12 ns, setup 26.89 ns,
    C2Q 17.17 ns; slack 24.06 ns a 25 MHz
    - Dimensione bitstream esatta: 104090 byte (101.6 KB)
    - Documento sale a 10 pagine
2026-06-11 feat: Rev 3 -- generic VERA_IS_PBI, PBI_ID_SEL, RAMBO_EN
    - Aggiunto generic VERA_IS_PBI (true=PBI, false=CCTL) per due bitstream
    distinti dallo stesso sorgente VHDL
    - DIP_SEL[1:0] sostituito da:
    PBI_ID_SEL: pin FPGA collegato via jumper HW a uno dei D[0..7];
    in PBI mode il valore campionato diventa VERA_CS latch
    RAMBO_EN: pullup=RAMbo abilitato, pulldown=disabilitato (HW override)
2026-06-11 docs: aggiunge sezione reset sequencer 74LVC1G08
    - LaTeX: nuova sezione 5 "Reset Sequencing" con boot sequence,
    equazioni logiche, schema ASCII circuito, tabella verita',
    spiegazione 74LVC vs 74HC (5V tolerant inputs), BOM (U1 + R1-R4)
    - README: nuova sottosezione hardware "Reset sequencer" con tabella
    fasi, equazioni, schema ASCII, note 74LVC, BOM compatta
    - PDF rigenerato: 12 pagine, 231 KB
2026-06-11 docs(fpga): update toolchain instructions for Debian 11
    - Recommended OSS CAD Suite for a modern and integrated toolchain.
    - Added detailed openFPGALoader build-from-source instructions.
    - Synchronized README.md and LaTeX documentation.
    - Regenerated build-and-programming-guide.pdf.
2026-06-12 chore: regenerate pbi_rom_pkg.vhd from vera_pbi_handler.bin
2026-06-19 docs: fix PIN-MAPPING.md — GPIO45/46 are A14/A15, not unused; correct XTAL and VDDA pins
    - A14/A15 remapped to GPIO45/46 (pin51/52) throughout: section header,
    descriptive paragraph, A12-A15 table, firmware decode snippet, U4 table,
    "GPIO disponibili" note, QFN56 full pinout
    - Critical Boot Warnings: GPIO45/46 now show A14/A15 signal with correct
    strapping description (pull-down → LOW; VDD_SPI from LDO ~1.8V; ROM msgs
    disabled — both safe for FN8)
